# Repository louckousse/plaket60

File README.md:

# Plaket60
## Based on [Plain60 Flex Edition rev2.2](https://github.com/evyd13/plain60-flex-edition)

### Modification from Plain60 Flex Edition rev2.2

- Removing the speaker
- Removing the usb port
- Removing the flex cut
- Removing some compatibility in layout (keeping a Tsangan bottom row)

### Features
- Compatible with QMK Firmware and VIA Configurator (if you flash a VIA compatible .hex file)
- Required JST header for connection with daughterboard
- ESD protection and fuse
- No LEDs and no underglow
- Minimal layout support
- ISP header

### Supported layouts

### Bill of materials (BOM)
Amount is per PCB, multiply as needed.

| LCSC part # | Description | Value | Package  | Amount |
| ----------- | ----------- | ----- | -------- | ------:|
| C49678      | Capacitor   | 0.1uF | 0805     | 4      |
| C1779       | Capacitor   | 4.7uF | 0805     | 1      |
| C28323      | Capacitor   | 1uF   | 0805     | 1      |
| C109001     | Diode       |       | 0805     | 64     |
| C261942     | Fuse        |       | 0805     | 1      |
| C17414      | Resistor    | 10K   | 0805     | 2      |
| C212411     | Resistor    | 5.1K  | 0805     | 2      |
| C17561      | Resistor    | 22    | 0805     | 2      |
| C44854      | MCU         | 32U4  | QFP-44   | 1      |
| C7519       | ESD chip    |       | SOT23-6  | 1      |
| C341521     | Resonator   | 16MHz | SMD      | 1      |
| C92584      | Switch      |       | SMD      | 1      |
| C2845363    | JST         |       | SMD      | 1      |

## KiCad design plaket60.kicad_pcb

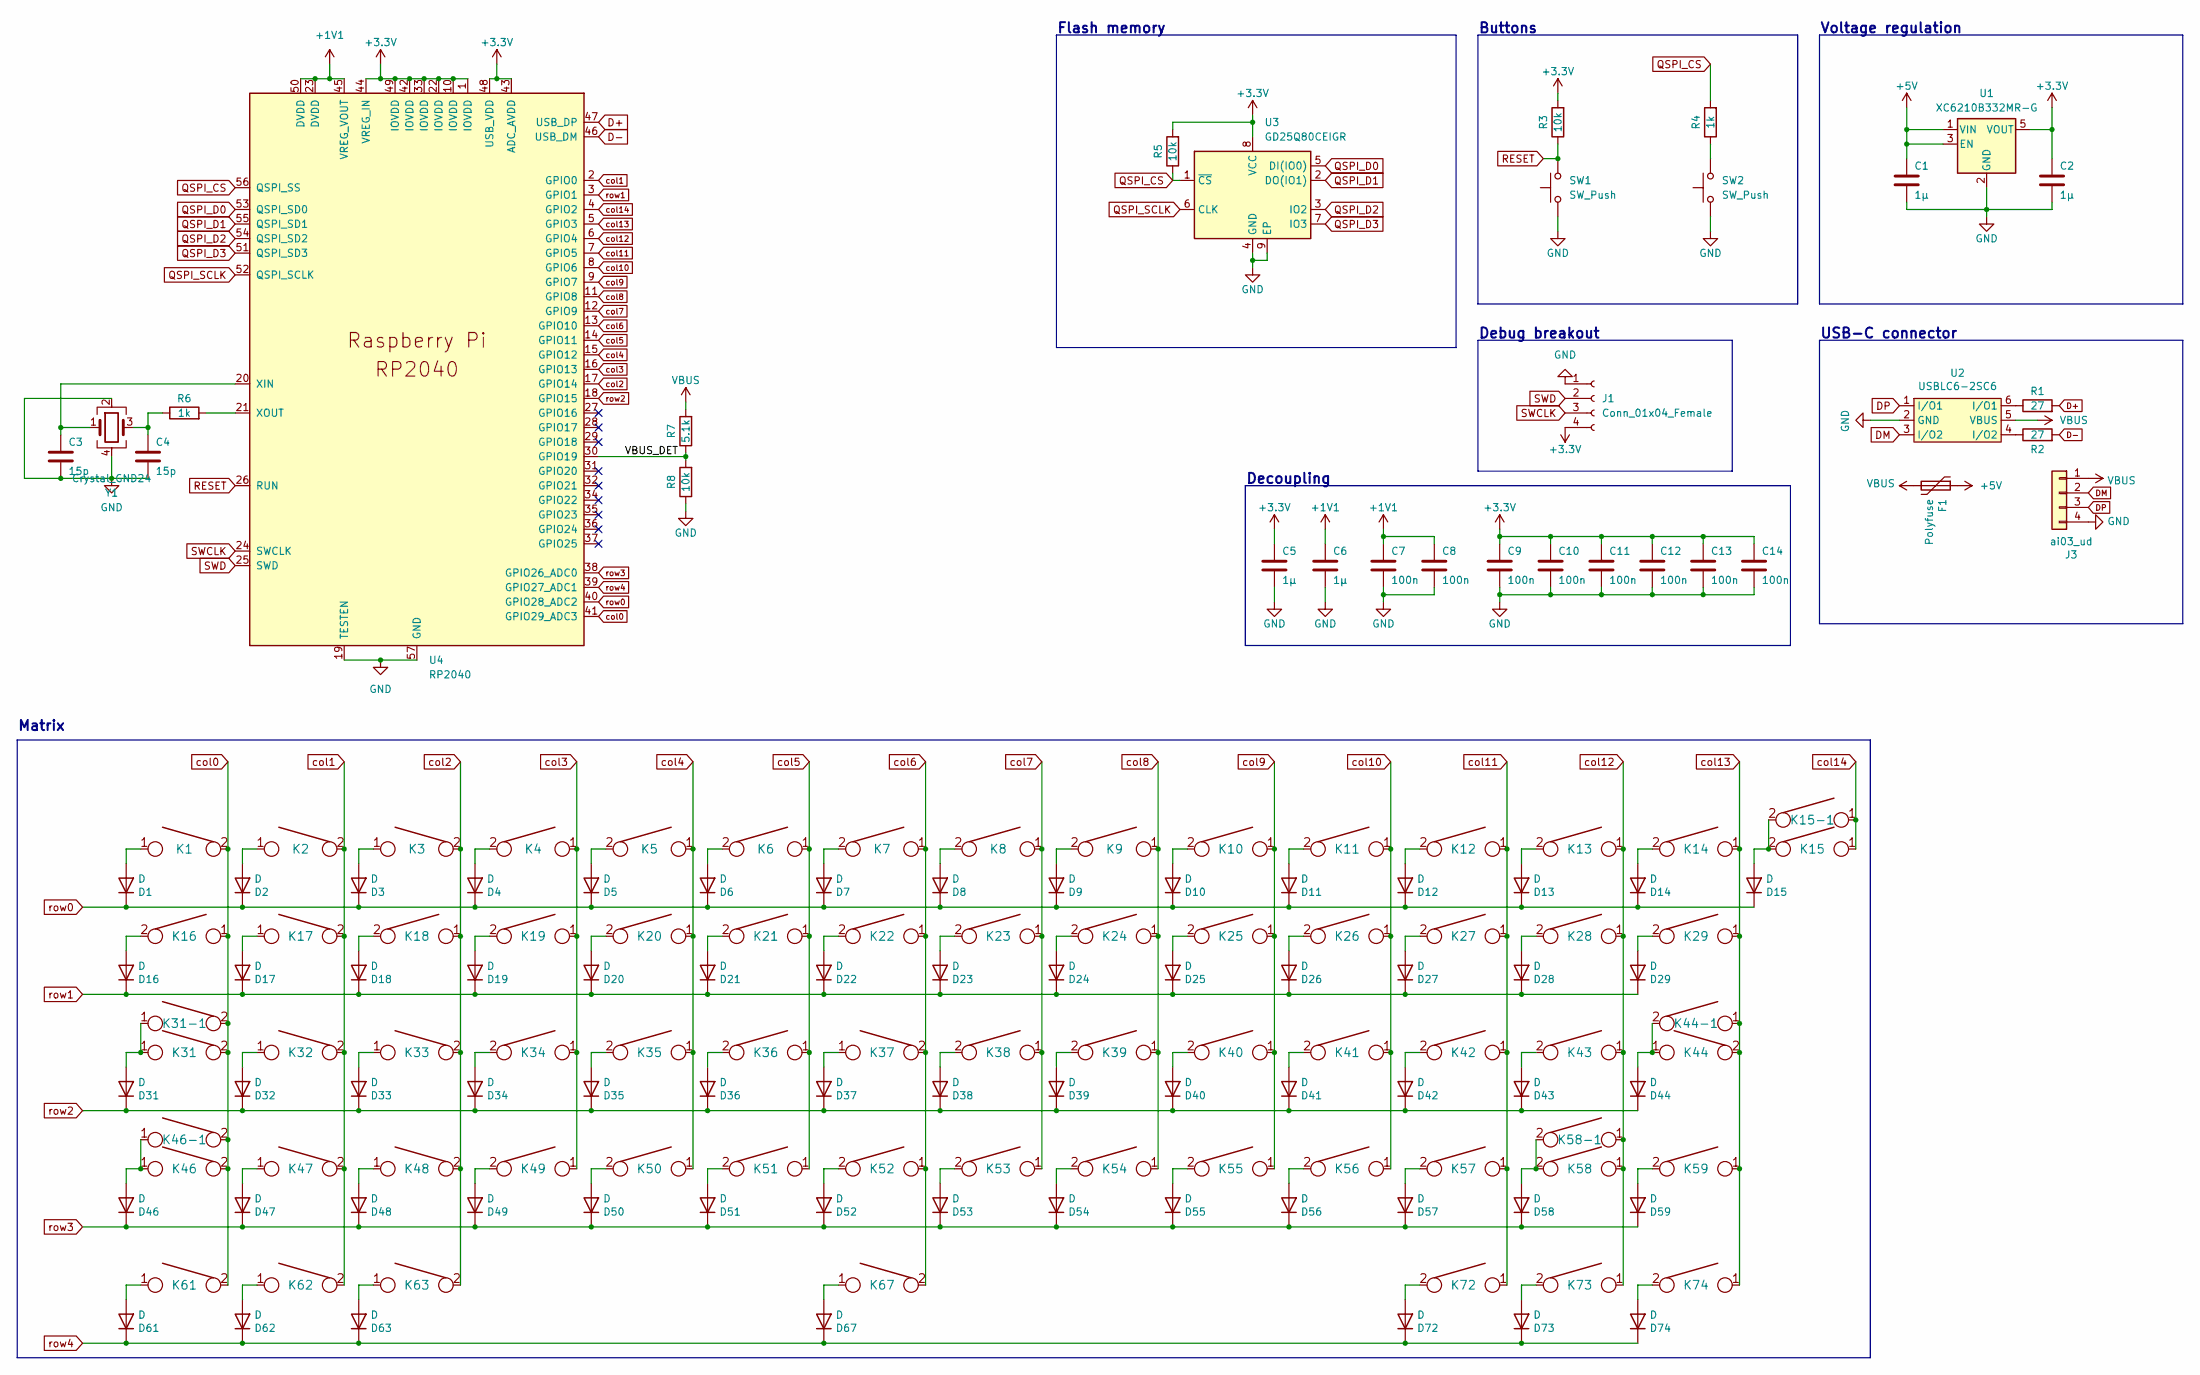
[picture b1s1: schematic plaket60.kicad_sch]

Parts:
C1, C2: 1µ; C_0402_1005Metric; LCSC C19666
C3, C4: 15p; C_0402_1005Metric; LCSC C1548
C5, C6: 1µ; C_0402_1005Metric; LCSC C52923
C7, C8, C9, C10, C11, C12, C13, C14: 100n; C_0402_1005Metric; LCSC C1525
D1, D2, D3, D4, D5, D6, D7, D8, D9, D10, D11, D12, D13, D14, D15, D16, D17, D18, D19, D20, D21, D22, D23, D24, D25, D26, D27, D28, D29, D31, D32, D33, D34, D35, D36, D37, D38, D39, D40, D41, D42, D43, D44, D46, D47, D48, D49, D50, D51, D52, D53, D54, D55, D56, D57, D58, D59, D61, D62, D63, D67, D72, D73, D74: D; D_0805
F1: Polyfuse; R_0805
J1: Conn_01x04_Female; PinHeader_1x04_P2.54mm_Vertical
J3: ai03_ud; JST_SH_SM04B-SRSS-TB_1x04-1MP_P1.00mm_Horizontal
K1, K2, K3, K4, K5, K6, K7, K8, K9, K10, K11, K12, K13, K14, K15-1, K17, K18, K19, K20, K21, K22, K23, K24, K25, K26, K27, K28, K32, K33, K34, K35, K36, K37, K38, K39, K40, K41, K42, K43, K47, K48, K49, K50, K51, K52, K53, K54, K55, K56, K57, K59, K62, K73: KEYSW; CHERRY_PLATE_100H
K15: KEYSW; CHERRY_PCB_200H
K16, K29, K61, K63, K72, K74: KEYSW; CHERRY_PLATE_150H
K31, K58-1: KEYSW; CHERRY_PLATE_175H
K31-1, K46-1: KEYSW; CHERRY_PLATE_125H
K44: KEYSW; CHERRY_PCB_225H_F
K44-1: KEYSW; CHERRY_PCB_200H_V
K46: KEYSW; CHERRY_PCB_225H
K58: KEYSW; CHERRY_PCB_275H
K67: KEYSW; CHERRY_PCB_700H_F
R1, R2: 27; R_0402_1005Metric; LCSC C25100
R3, R5, R8: 10k; R_0402_1005Metric; LCSC C25744
R4, R6: 1k; R_0402_1005Metric; LCSC C11702
R7: 5.1k; R_0402_1005Metric; LCSC C25905
SW1, SW2: SW_Push; SW_SPST_TL3342; LCSC C319433
U1: XC6210B332MR-G; SOT-23-5; LCSC C82942
U2: USBLC6-2SC6; Farnell 1295310
U3: GD25Q80CEIGR; USON-8-1EP_3x2mm_P0.5mm_EP0.25x1.65mm; LCSC C395484
U4: RP2040; RP2040-QFN-56
Y1: Crystal_GND24; Crystal_SMD_3225-4Pin_3.2x2.5mm

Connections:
+1V1: C6.1, C7.1, C8.1, U4.23 (DVDD), U4.45 (VREG_VOUT), U4.50 (DVDD)
+3V3: C2.1, C5.1, C9.1, C10.1, C11.1, C12.1, C13.1, C14.1, J1.4, R3.2, R5.2, U1.5 (VOUT), U3.8 (VCC), U4.1 (IOVDD), U4.10 (IOVDD), U4.22 (IOVDD), U4.33 (IOVDD), U4.42 (IOVDD), U4.43 (ADC_AVDD), U4.44 (VREG_IN), U4.48 (USB_VDD), U4.49 (IOVDD)
+5V: C1.1, F1.1, U1.1 (VIN), U1.3 (EN)
/VBUS_DET: R7.1, R8.2, U4.30 (GPIO19)
D+: R1.2, U4.47 (USB_DP)
D-: R2.2, U4.46 (USB_DM)
DM: J3.2, U2.3 (I/O2)
DP: J3.3, U2.1 (I/O1)
GND: C1.2, C2.2, C3.2, C4.2, C5.2, C6.2, C7.2, C8.2, C9.2, C10.2, C11.2, C12.2, C13.2, C14.2, J1.1, J3.4, R8.1, SW1.1, SW2.1, U1.2 (GND), U2.2 (GND), U3.4 (GND), U3.9 (EP), U4.19 (TESTEN), U4.57 (GND), Y1.2, Y1.4
unnamed: C3.1, U4.20 (XIN), Y1.1
unnamed: C4.1, R6.1, Y1.3
unnamed: D1.2 (A), K1.1
unnamed: D2.2 (A), K2.1
unnamed: D3.2 (A), K3.1
unnamed: D4.2 (A), K4.2
unnamed: D5.2 (A), K5.2
unnamed: D6.2 (A), K6.2
unnamed: D7.2 (A), K7.2
unnamed: D8.2 (A), K8.2
unnamed: D9.2 (A), K9.2
unnamed: D10.2 (A), K10.2
unnamed: D11.2 (A), K11.2
unnamed: D12.2 (A), K12.2
unnamed: D13.2 (A), K13.2
unnamed: D14.2 (A), K14.2
unnamed: D15.2 (A), K15.2, K15-1.2
unnamed: D16.2 (A), K16.2
unnamed: D17.2 (A), K17.1
unnamed: D18.2 (A), K18.2
unnamed: D19.2 (A), K19.2
unnamed: D20.2 (A), K20.2
unnamed: D21.2 (A), K21.2
unnamed: D22.2 (A), K22.2
unnamed: D23.2 (A), K23.2
unnamed: D24.2 (A), K24.2
unnamed: D25.2 (A), K25.2
unnamed: D26.2 (A), K26.2
unnamed: D27.2 (A), K27.2
unnamed: D28.2 (A), K28.2
unnamed: D29.2 (A), K29.2
unnamed: D31.2 (A), K31.1, K31-1.1
unnamed: D32.2 (A), K32.1
unnamed: D33.2 (A), K33.1
unnamed: D34.2 (A), K34.2
unnamed: D35.2 (A), K35.2
unnamed: D36.2 (A), K36.2
unnamed: D37.2 (A), K37.1
unnamed: D38.2 (A), K38.2
unnamed: D39.2 (A), K39.2
unnamed: D40.2 (A), K40.2
unnamed: D41.2 (A), K41.2
unnamed: D42.2 (A), K42.2
unnamed: D43.2 (A), K43.2
unnamed: D44.2 (A), K44.1, K44-1.2
unnamed: D46.2 (A), K46.1, K46-1.1
unnamed: D47.2 (A), K47.1
unnamed: D48.2 (A), K48.1
unnamed: D49.2 (A), K49.2
unnamed: D50.2 (A), K50.2
unnamed: D51.2 (A), K51.2
unnamed: D52.2 (A), K52.2
unnamed: D53.2 (A), K53.2
unnamed: D54.2 (A), K54.2
unnamed: D55.2 (A), K55.2
unnamed: D56.2 (A), K56.2
unnamed: D57.2 (A), K57.2
unnamed: D58.2 (A), K58.2, K58-1.2
unnamed: D59.2 (A), K59.2
unnamed: D61.2 (A), K61.1
unnamed: D62.2 (A), K62.1
unnamed: D63.2 (A), K63.1
unnamed: D67.2 (A), K67.1
unnamed: D72.2 (A), K72.2
unnamed: D73.2 (A), K73.2
unnamed: D74.2 (A), K74.2
unnamed: R1.1, U2.6 (I/O1)
unnamed: R2.1, U2.4 (I/O2)
unnamed: R4.1, SW2.2
unnamed: R6.2, U4.21 (XOUT)
QSPI_CS: R4.2, R5.1, U3.1 (~CS), U4.56 (QSPI_SS)
QSPI_D0: U3.5 (DI(IO0)), U4.53 (QSPI_SD0)
QSPI_D1: U3.2 (DO(IO1)), U4.55 (QSPI_SD1)
QSPI_D2: U3.3 (IO2), U4.54 (QSPI_SD2)
QSPI_D3: U3.7 (IO3), U4.51 (QSPI_SD3)
QSPI_SCLK: U3.6 (CLK), U4.52 (QSPI_SCLK)
RESET: R3.1, SW1.2, U4.26 (RUN)
SWCLK: J1.3, U4.24 (SWCLK)
SWD: J1.2, U4.25 (SWD)
VBUS: F1.2, J3.1, R7.2, U2.5 (VBUS)
col0: K1.2, K16.1, K31.2, K31-1.2, K46.2, K46-1.2, K61.2, U4.41 (GPIO29_ADC3)
col1: K2.2, K17.2, K32.2, K47.2, K62.2, U4.2 (GPIO0)
col2: K3.2, K18.1, K33.2, K48.2, K63.2, U4.17 (GPIO14)
col3: K4.1, K19.1, K34.1, K49.1, U4.16 (GPIO13)
col4: K5.1, K20.1, K35.1, K50.1, U4.15 (GPIO12)
col5: K6.1, K21.1, K36.1, K51.1, U4.14 (GPIO11)
col6: K7.1, K22.1, K37.2, K52.1, K67.2, U4.13 (GPIO10)
col7: K8.1, K23.1, K38.1, K53.1, U4.12 (GPIO9)
col8: K9.1, K24.1, K39.1, K54.1, U4.11 (GPIO8)
col9: K10.1, K25.1, K40.1, K55.1, U4.9 (GPIO7)
col10: K11.1, K26.1, K41.1, K56.1, U4.8 (GPIO6)
col11: K12.1, K27.1, K42.1, K57.1, K72.1, U4.7 (GPIO5)
col12: K13.1, K28.1, K43.1, K58.1, K58-1.1, K73.1, U4.6 (GPIO4)
col13: K14.1, K29.1, K44.2, K44-1.1, K59.1, K74.1, U4.5 (GPIO3)
col14: K15.1, K15-1.1, U4.4 (GPIO2)
row0: D1.1 (K), D2.1 (K), D3.1 (K), D4.1 (K), D5.1 (K), D6.1 (K), D7.1 (K), D8.1 (K), D9.1 (K), D10.1 (K), D11.1 (K), D12.1 (K), D13.1 (K), D14.1 (K), D15.1 (K), U4.40 (GPIO28_ADC2)
row1: D16.1 (K), D17.1 (K), D18.1 (K), D19.1 (K), D20.1 (K), D21.1 (K), D22.1 (K), D23.1 (K), D24.1 (K), D25.1 (K), D26.1 (K), D27.1 (K), D28.1 (K), D29.1 (K), U4.3 (GPIO1)
row2: D31.1 (K), D32.1 (K), D33.1 (K), D34.1 (K), D35.1 (K), D36.1 (K), D37.1 (K), D38.1 (K), D39.1 (K), D40.1 (K), D41.1 (K), D42.1 (K), D43.1 (K), D44.1 (K), U4.18 (GPIO15)
row3: D46.1 (K), D47.1 (K), D48.1 (K), D49.1 (K), D50.1 (K), D51.1 (K), D52.1 (K), D53.1 (K), D54.1 (K), D55.1 (K), D56.1 (K), D57.1 (K), D58.1 (K), D59.1 (K), U4.38 (GPIO26_ADC0)
row4: D61.1 (K), D62.1 (K), D63.1 (K), D67.1 (K), D72.1 (K), D73.1 (K), D74.1 (K), U4.39 (GPIO27_ADC1)

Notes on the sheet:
Buttons
Voltage regulation
Flash memory
Decoupling
USB-C connector
Matrix
Debug breakout

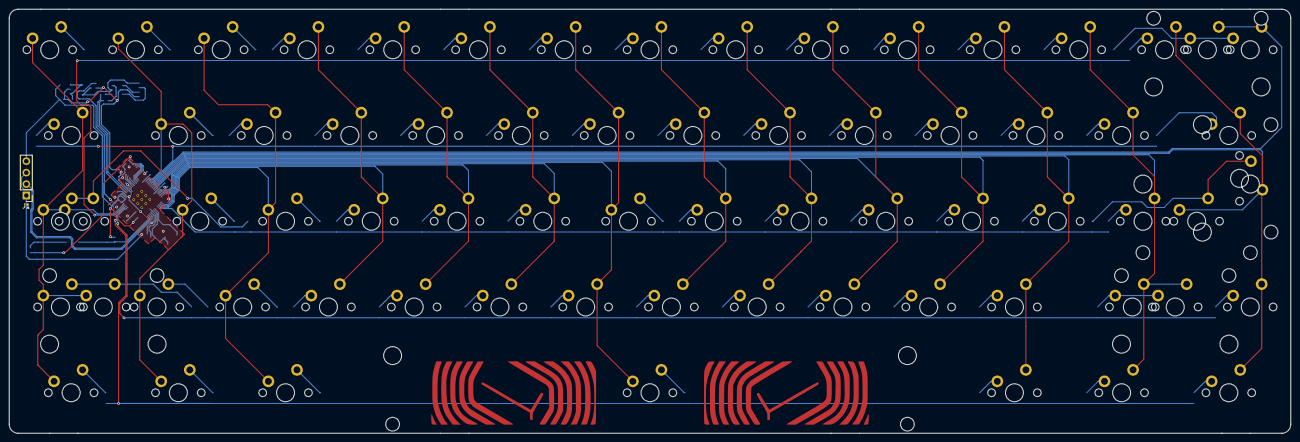
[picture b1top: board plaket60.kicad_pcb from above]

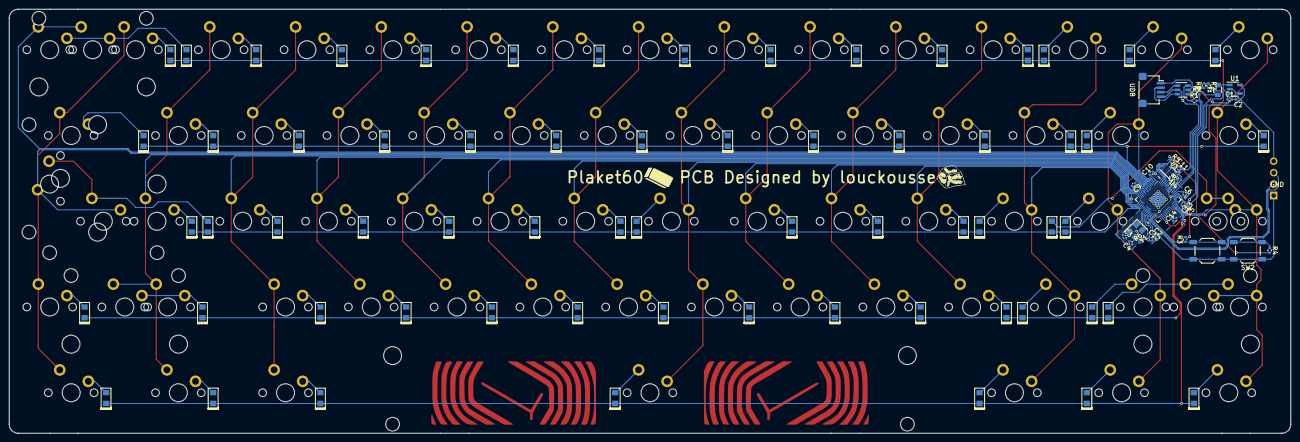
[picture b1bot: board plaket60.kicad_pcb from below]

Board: 2 copper layers, 284.7 x 94.2 mm, 165 parts (95 on the bottom side), 109 nets.

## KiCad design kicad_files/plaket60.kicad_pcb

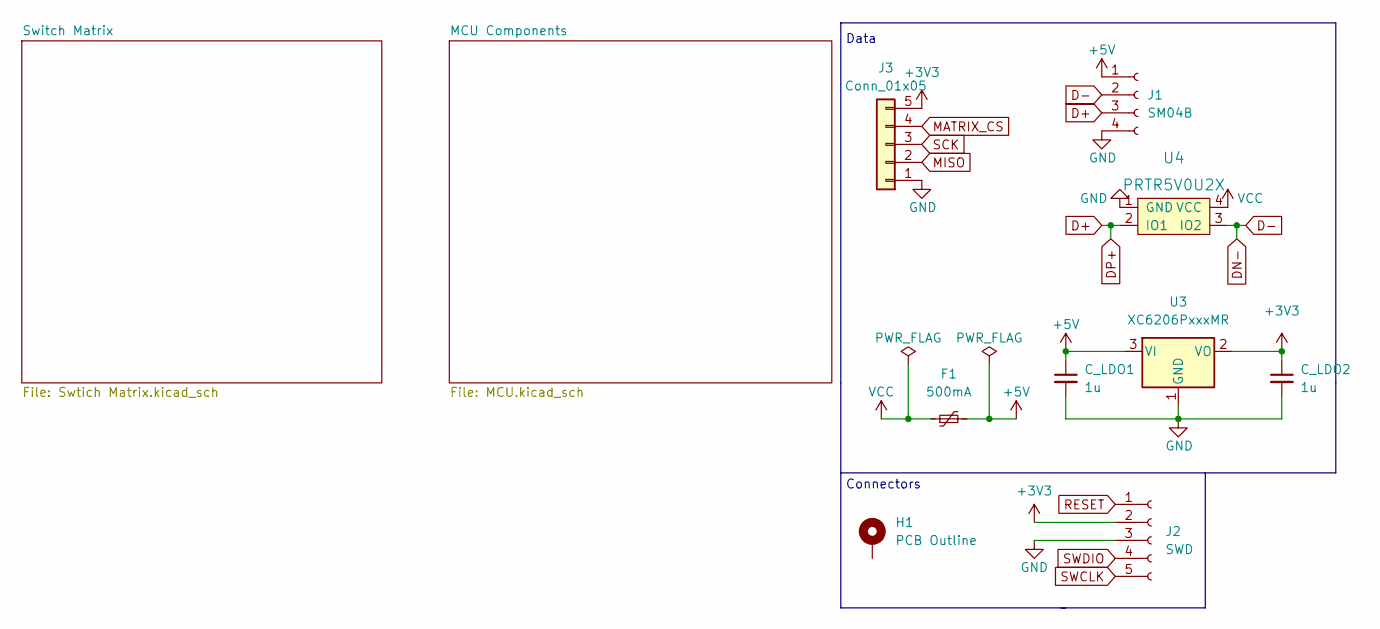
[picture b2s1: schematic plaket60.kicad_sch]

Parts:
C_LDO1, C_LDO2: 1u; C_0402_1005Metric
F1: 500mA; Fuse_0805_2012Metric
H1: PCB Outline; L60 Outline
J1: SM04B; JST_SH_SM04B-SRSS-TB_1x04-1MP_P1.00mm_Horizontal
J2: SWD; PinHeader_1x05_P2.54mm_Vertical
J3: Conn_01x05; JST_SH_SM05B-SRSS-TB_1x05-1MP_P1.00mm_Horizontal
U3: XC6206PxxxMR; SOT-23
U4: PRTR5V0U2X; SOT143B

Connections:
+3V3: C_LDO2.1, J2.2, J3.5, U3.2 (VO); also elsewhere on the board
+5V: C_LDO1.1, F1.2, J1.1, U3.3 (VI)
D+: J1.3, U4.2 (IO1); also elsewhere on the board
D-: J1.2, U4.3 (IO2); also elsewhere on the board
GND: C_LDO1.2, C_LDO2.2, J1.4, J2.3, J3.1, U3.1 (GND), U4.1 (GND); also elsewhere on the board
MATRIX_CS: J3.4; also elsewhere on the board
MISO: J3.2; also elsewhere on the board
RESET: J2.1; also elsewhere on the board
SCK: J3.3; also elsewhere on the board
SWCLK: J2.5; also elsewhere on the board
SWDIO: J2.4; also elsewhere on the board
VCC: F1.1, U4.4 (VCC)

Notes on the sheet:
Connectors
Data

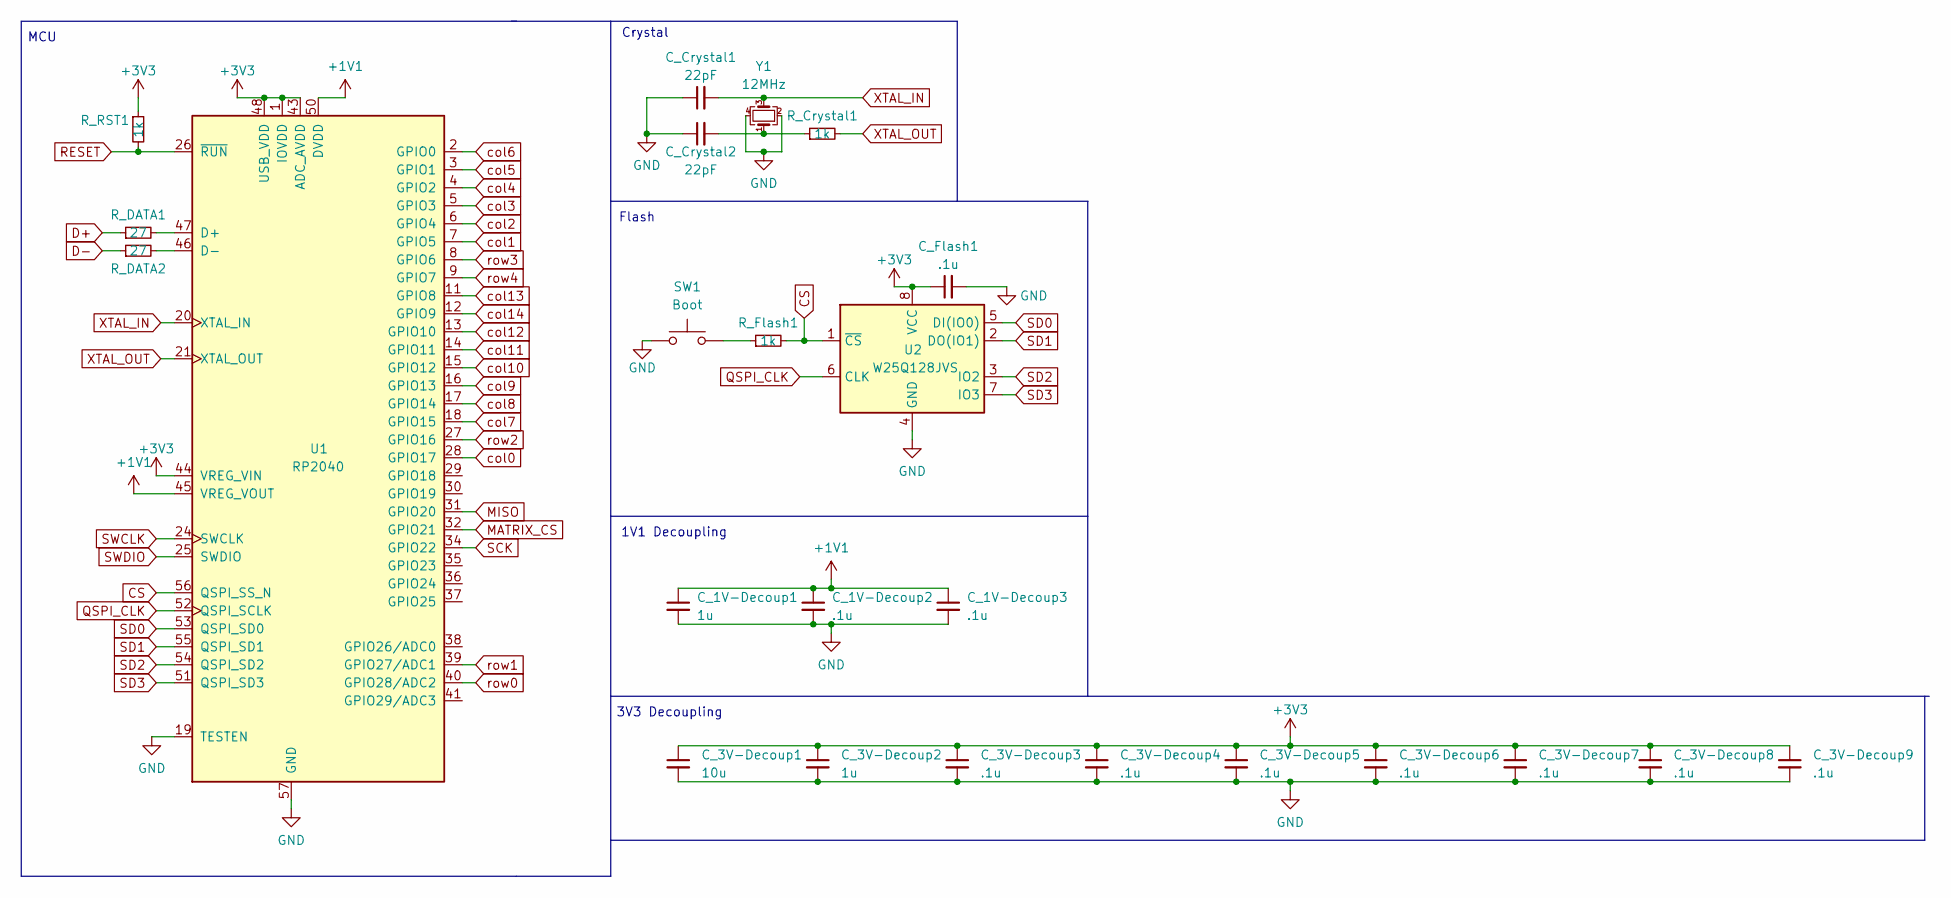
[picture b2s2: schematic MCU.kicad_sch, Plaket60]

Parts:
C_1V-Decoup1, C_3V-Decoup2: 1u; C_0402_1005Metric
C_1V-Decoup2, C_1V-Decoup3, C_3V-Decoup3, C_3V-Decoup4, C_3V-Decoup5, C_3V-Decoup6, C_3V-Decoup7, C_3V-Decoup8, C_3V-Decoup9: .1u; C_0402_1005Metric
C_3V-Decoup1: 10u; C_0402_1005Metric
C_Crystal1, C_Crystal2: 22pF; C_0402_1005Metric
C_Flash1: .1u; C_0402_1005Metric
R_Crystal1: 1k; R_0402_1005Metric
R_DATA1, R_DATA2: 27; R_0402_1005Metric
R_Flash1: 1k; R_0402_1005Metric
R_RST1: 1k; R_0402_1005Metric
SW1: Boot; PinHeader_1x02_P2.54mm_Vertical
U1: RP2040; RP2040-QFN-56
U2: W25Q128JVS; SOIC-8_5.23x5.23mm_P1.27mm
Y1: 12MHz; Crystal_SMD_3225-4Pin_3.2x2.5mm

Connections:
+1V1: C_1V-Decoup1.1, C_1V-Decoup2.1, C_1V-Decoup3.1, U1.23 (DVDD), U1.45 (VREG_VOUT), U1.50 (DVDD)
+3V3: C_3V-Decoup1.1, C_3V-Decoup2.1, C_3V-Decoup3.1, C_3V-Decoup4.1, C_3V-Decoup5.1, C_3V-Decoup6.1, C_3V-Decoup7.1, C_3V-Decoup8.1, C_3V-Decoup9.1, C_Flash1.1, R_RST1.1, U1.1 (IOVDD), U1.10 (IOVDD), U1.22 (IOVDD), U1.33 (IOVDD), U1.42 (IOVDD), U1.43 (ADC_AVDD), U1.44 (VREG_VIN), U1.48 (USB_VDD), U1.49 (IOVDD), U2.8 (VCC); also elsewhere on the board
CS: R_Flash1.2, U1.56 (QSPI_SS_N), U2.1 (~CS)
D+: R_DATA1.1; also elsewhere on the board
D-: R_DATA2.1; also elsewhere on the board
GND: C_1V-Decoup1.2, C_1V-Decoup2.2, C_1V-Decoup3.2, C_3V-Decoup1.2, C_3V-Decoup2.2, C_3V-Decoup3.2, C_3V-Decoup4.2, C_3V-Decoup5.2, C_3V-Decoup6.2, C_3V-Decoup7.2, C_3V-Decoup8.2, C_3V-Decoup9.2, C_Crystal1.1, C_Crystal2.1, C_Flash1.2, SW1.1, U1.19 (TESTEN), U1.57 (GND), U2.4 (GND), Y1.2, Y1.4; also elsewhere on the board
MATRIX_CS: U1.32 (GPIO21); also elsewhere on the board
MISO: U1.31 (GPIO20); also elsewhere on the board
unnamed: C_Crystal2.2, R_Crystal1.1, Y1.1
unnamed: R_Flash1.1, SW1.2
unnamed: R_DATA1.2, U1.47 (D+)
unnamed: R_DATA2.2, U1.46 (D-)
QSPI_CLK: U1.52 (QSPI_SCLK), U2.6 (CLK)
RESET: R_RST1.2, U1.26 (~RUN); also elsewhere on the board
SCK: U1.34 (GPIO22); also elsewhere on the board
SD0: U1.53 (QSPI_SD0), U2.5 (DI(IO0))
SD1: U1.55 (QSPI_SD1), U2.2 (DO(IO1))
SD2: U1.54 (QSPI_SD2), U2.3 (IO2)
SD3: U1.51 (QSPI_SD3), U2.7 (IO3)
SWCLK: U1.24 (SWCLK); also elsewhere on the board
SWDIO: U1.25 (SWDIO); also elsewhere on the board
XTAL_IN: C_Crystal1.2, U1.20 (XTAL_IN), Y1.3
XTAL_OUT: R_Crystal1.2, U1.21 (XTAL_OUT)
col0: U1.28 (GPIO17); also elsewhere on the board
col1: U1.7 (GPIO5); also elsewhere on the board
col2: U1.6 (GPIO4); also elsewhere on the board
col3: U1.5 (GPIO3); also elsewhere on the board
col4: U1.4 (GPIO2); also elsewhere on the board
col5: U1.3 (GPIO1); also elsewhere on the board
col6: U1.2 (GPIO0); also elsewhere on the board
col7: U1.18 (GPIO15); also elsewhere on the board
col8: U1.17 (GPIO14); also elsewhere on the board
col9: U1.16 (GPIO13); also elsewhere on the board
col10: U1.15 (GPIO12); also elsewhere on the board
col11: U1.14 (GPIO11); also elsewhere on the board
col12: U1.13 (GPIO10); also elsewhere on the board
col13: U1.11 (GPIO8); also elsewhere on the board
col14: U1.12 (GPIO9); also elsewhere on the board
row0: U1.40 (GPIO28/ADC2); also elsewhere on the board
row1: U1.39 (GPIO27/ADC1); also elsewhere on the board
row2: U1.27 (GPIO16); also elsewhere on the board
row3: U1.8 (GPIO6); also elsewhere on the board
row4: U1.9 (GPIO7); also elsewhere on the board

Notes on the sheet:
Flash
MCU
Crystal
3V3 Decoupling
1V1 Decoupling

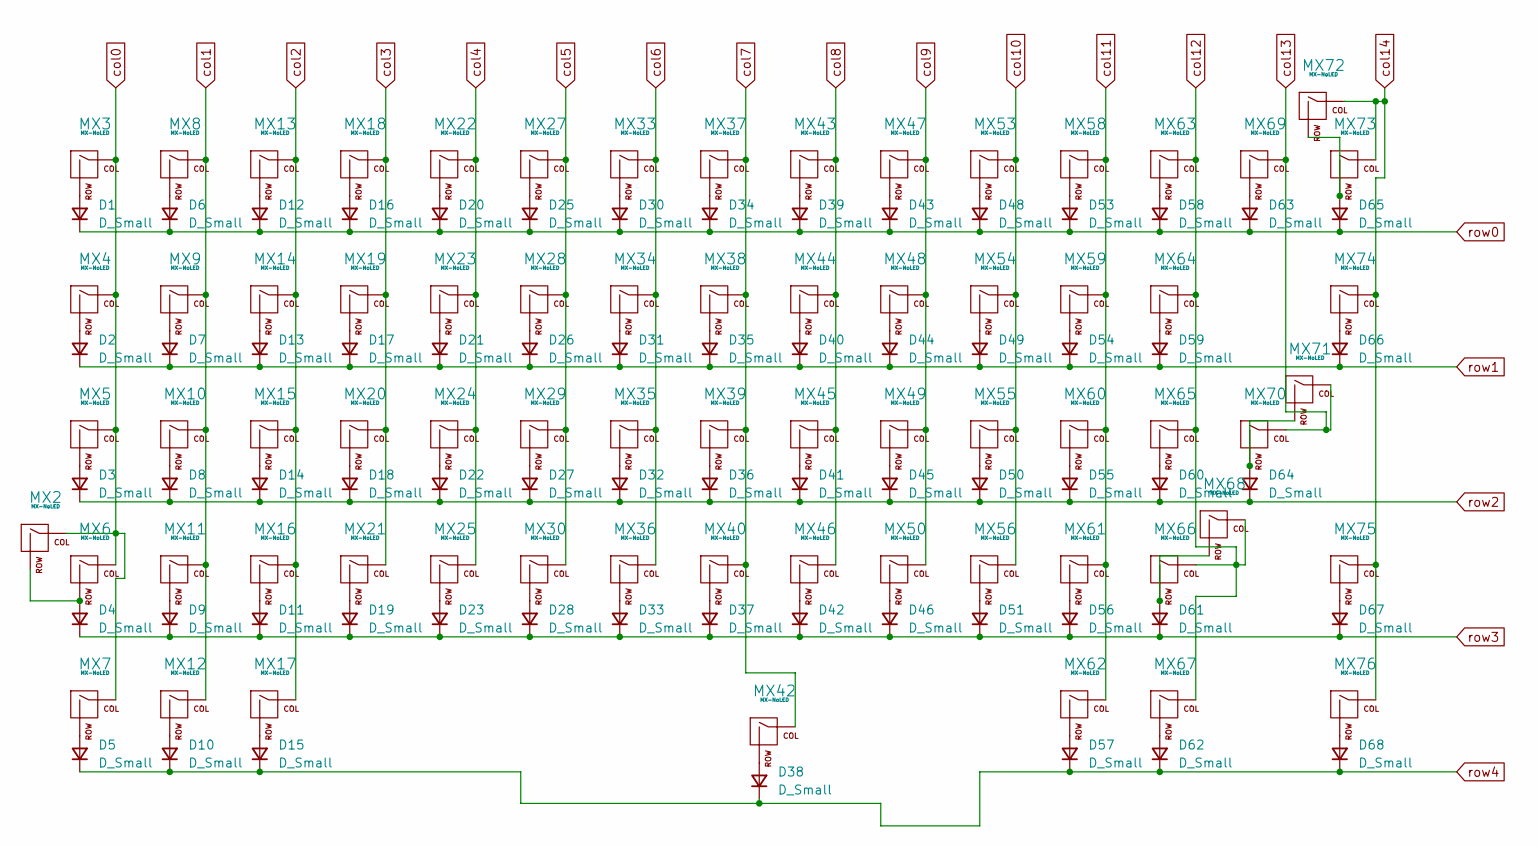
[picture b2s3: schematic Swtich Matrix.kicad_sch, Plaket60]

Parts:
D1, D2, D3, D4, D5, D6, D7, D8, D9, D10, D11, D12, D13, D14, D15, D16, D17, D18, D19, D20, D21, D22, D23, D25, D26, D27, D28, D30, D31, D32, D33, D34, D35, D36, D37, D38, D39, D40, D41, D42, D43, D44, D45, D46, D48, D49, D50, D51, D53, D54, D55, D56, D57, D58, D59, D60, D61, D62, D63, D64, D65, D66, D67, D68: D_Small; D_SOD-123
MX2: MX-NoLED; mx_125u
MX3, MX8, MX9, MX10, MX11, MX12, MX13, MX14, MX15, MX16, MX18, MX19, MX20, MX21, MX22, MX23, MX24, MX25, MX27, MX28, MX29, MX30, MX33, MX34, MX35, MX36, MX37, MX38, MX39, MX40, MX43, MX44, MX45, MX46, MX47, MX48, MX49, MX50, MX53, MX54, MX55, MX56, MX58, MX59, MX60, MX61, MX63, MX64, MX65, MX67, MX69, MX73, MX75: MX-NoLED; mx_1u
MX4, MX7, MX17, MX62, MX74, MX76: MX-NoLED; mx_15u
MX5: MX-NoLED; mx_stepped_caps
MX6, MX70: MX-NoLED; mx_225u
MX42: MX-NoLED; mx_7u
MX66: MX-NoLED; mx_175u
MX68: MX-NoLED; mx_275u
MX71: MX-NoLED; mx_iso
MX72: MX-NoLED; mx_2u

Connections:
unnamed: D1.2 (A), MX3.2 (ROW)
unnamed: D2.2 (A), MX4.2 (ROW)
unnamed: D3.2 (A), MX5.2 (ROW)
unnamed: D4.2 (A), MX2.2 (ROW), MX6.2 (ROW)
unnamed: D5.2 (A), MX7.2 (ROW)
unnamed: D6.2 (A), MX8.2 (ROW)
unnamed: D7.2 (A), MX9.2 (ROW)
unnamed: D8.2 (A), MX10.2 (ROW)
unnamed: D9.2 (A), MX11.2 (ROW)
unnamed: D10.2 (A), MX12.2 (ROW)
unnamed: D11.2 (A), MX16.2 (ROW)
unnamed: D12.2 (A), MX13.2 (ROW)
unnamed: D13.2 (A), MX14.2 (ROW)
unnamed: D14.2 (A), MX15.2 (ROW)
unnamed: D15.2 (A), MX17.2 (ROW)
unnamed: D16.2 (A), MX18.2 (ROW)
unnamed: D17.2 (A), MX19.2 (ROW)
unnamed: D18.2 (A), MX20.2 (ROW)
unnamed: D19.2 (A), MX21.2 (ROW)
unnamed: D20.2 (A), MX22.2 (ROW)
unnamed: D21.2 (A), MX23.2 (ROW)
unnamed: D22.2 (A), MX24.2 (ROW)
unnamed: D23.2 (A), MX25.2 (ROW)
unnamed: D25.2 (A), MX27.2 (ROW)
unnamed: D26.2 (A), MX28.2 (ROW)
unnamed: D27.2 (A), MX29.2 (ROW)
unnamed: D28.2 (A), MX30.2 (ROW)
unnamed: D30.2 (A), MX33.2 (ROW)
unnamed: D31.2 (A), MX34.2 (ROW)
unnamed: D32.2 (A), MX35.2 (ROW)
unnamed: D33.2 (A), MX36.2 (ROW)
unnamed: D34.2 (A), MX37.2 (ROW)
unnamed: D35.2 (A), MX38.2 (ROW)
unnamed: D36.2 (A), MX39.2 (ROW)
unnamed: D37.2 (A), MX40.2 (ROW)
unnamed: D38.2 (A), MX42.2 (ROW)
unnamed: D39.2 (A), MX43.2 (ROW)
unnamed: D40.2 (A), MX44.2 (ROW)
unnamed: D41.2 (A), MX45.2 (ROW)
unnamed: D42.2 (A), MX46.2 (ROW)
unnamed: D43.2 (A), MX47.2 (ROW)
unnamed: D44.2 (A), MX48.2 (ROW)
unnamed: D45.2 (A), MX49.2 (ROW)
unnamed: D46.2 (A), MX50.2 (ROW)
unnamed: D48.2 (A), MX53.2 (ROW)
unnamed: D49.2 (A), MX54.2 (ROW)
unnamed: D50.2 (A), MX55.2 (ROW)
unnamed: D51.2 (A), MX56.2 (ROW)
unnamed: D53.2 (A), MX58.2 (ROW)
unnamed: D54.2 (A), MX59.2 (ROW)
unnamed: D55.2 (A), MX60.2 (ROW)
unnamed: D56.2 (A), MX61.2 (ROW)
unnamed: D57.2 (A), MX62.2 (ROW)
unnamed: D58.2 (A), MX63.2 (ROW)
unnamed: D59.2 (A), MX64.2 (ROW)
unnamed: D60.2 (A), MX65.2 (ROW)
unnamed: D61.2 (A), MX66.2 (ROW), MX68.2 (ROW)
unnamed: D62.2 (A), MX67.2 (ROW)
unnamed: D63.2 (A), MX69.2 (ROW)
unnamed: D64.2 (A), MX70.2 (ROW), MX71.2 (ROW)
unnamed: D65.2 (A), MX72.2 (ROW), MX73.2 (ROW)
unnamed: D66.2 (A), MX74.2 (ROW)
unnamed: D67.2 (A), MX75.2 (ROW)
unnamed: D68.2 (A), MX76.2 (ROW)
col0: MX2.1 (COL), MX3.1 (COL), MX4.1 (COL), MX5.1 (COL), MX6.1 (COL), MX7.1 (COL); also elsewhere on the board
col1: MX8.1 (COL), MX9.1 (COL), MX10.1 (COL), MX11.1 (COL), MX12.1 (COL); also elsewhere on the board
col2: MX13.1 (COL), MX14.1 (COL), MX15.1 (COL), MX16.1 (COL), MX17.1 (COL); also elsewhere on the board
col3: MX18.1 (COL), MX19.1 (COL), MX20.1 (COL), MX21.1 (COL); also elsewhere on the board
col4: MX22.1 (COL), MX23.1 (COL), MX24.1 (COL), MX25.1 (COL); also elsewhere on the board
col5: MX27.1 (COL), MX28.1 (COL), MX29.1 (COL), MX30.1 (COL); also elsewhere on the board
col6: MX33.1 (COL), MX34.1 (COL), MX35.1 (COL), MX36.1 (COL); also elsewhere on the board
col7: MX37.1 (COL), MX38.1 (COL), MX39.1 (COL), MX40.1 (COL), MX42.1 (COL); also elsewhere on the board
col8: MX43.1 (COL), MX44.1 (COL), MX45.1 (COL), MX46.1 (COL); also elsewhere on the board
col9: MX47.1 (COL), MX48.1 (COL), MX49.1 (COL), MX50.1 (COL); also elsewhere on the board
col10: MX53.1 (COL), MX54.1 (COL), MX55.1 (COL), MX56.1 (COL); also elsewhere on the board
col11: MX58.1 (COL), MX59.1 (COL), MX60.1 (COL), MX61.1 (COL), MX62.1 (COL); also elsewhere on the board
col12: MX63.1 (COL), MX64.1 (COL), MX65.1 (COL), MX66.1 (COL), MX67.1 (COL), MX68.1 (COL); also elsewhere on the board
col13: MX69.1 (COL), MX70.1 (COL), MX71.1 (COL); also elsewhere on the board
col14: MX72.1 (COL), MX73.1 (COL), MX74.1 (COL), MX75.1 (COL), MX76.1 (COL); also elsewhere on the board
row0: D1.1 (K), D6.1 (K), D12.1 (K), D16.1 (K), D20.1 (K), D25.1 (K), D30.1 (K), D34.1 (K), D39.1 (K), D43.1 (K), D48.1 (K), D53.1 (K), D58.1 (K), D63.1 (K), D65.1 (K); also elsewhere on the board
row1: D2.1 (K), D7.1 (K), D13.1 (K), D17.1 (K), D21.1 (K), D26.1 (K), D31.1 (K), D35.1 (K), D40.1 (K), D44.1 (K), D49.1 (K), D54.1 (K), D59.1 (K), D66.1 (K); also elsewhere on the board
row2: D3.1 (K), D8.1 (K), D14.1 (K), D18.1 (K), D22.1 (K), D27.1 (K), D32.1 (K), D36.1 (K), D41.1 (K), D45.1 (K), D50.1 (K), D55.1 (K), D60.1 (K), D64.1 (K); also elsewhere on the board
row3: D4.1 (K), D9.1 (K), D11.1 (K), D19.1 (K), D23.1 (K), D28.1 (K), D33.1 (K), D37.1 (K), D42.1 (K), D46.1 (K), D51.1 (K), D56.1 (K), D61.1 (K), D67.1 (K); also elsewhere on the board
row4: D5.1 (K), D10.1 (K), D15.1 (K), D38.1 (K), D57.1 (K), D62.1 (K), D68.1 (K); also elsewhere on the board

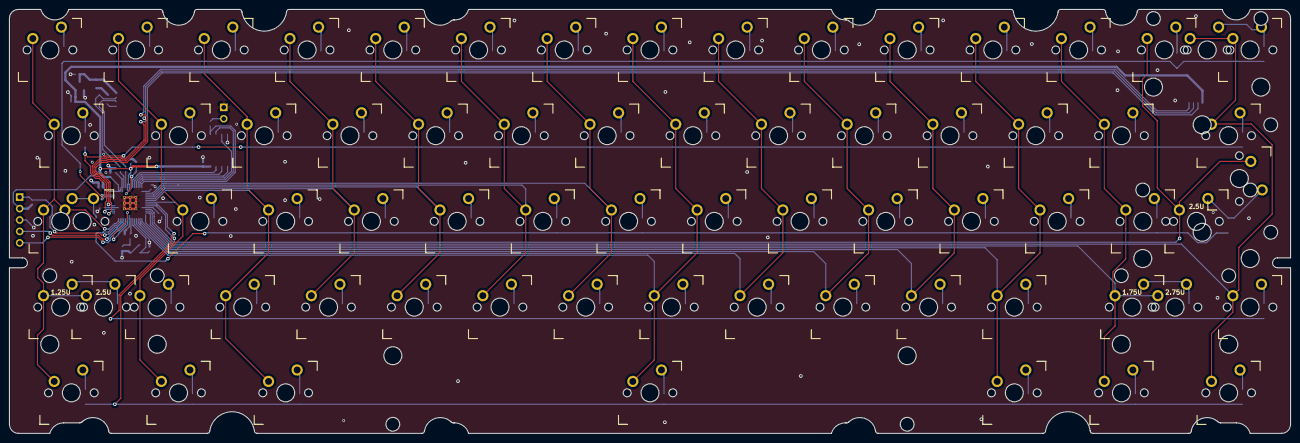
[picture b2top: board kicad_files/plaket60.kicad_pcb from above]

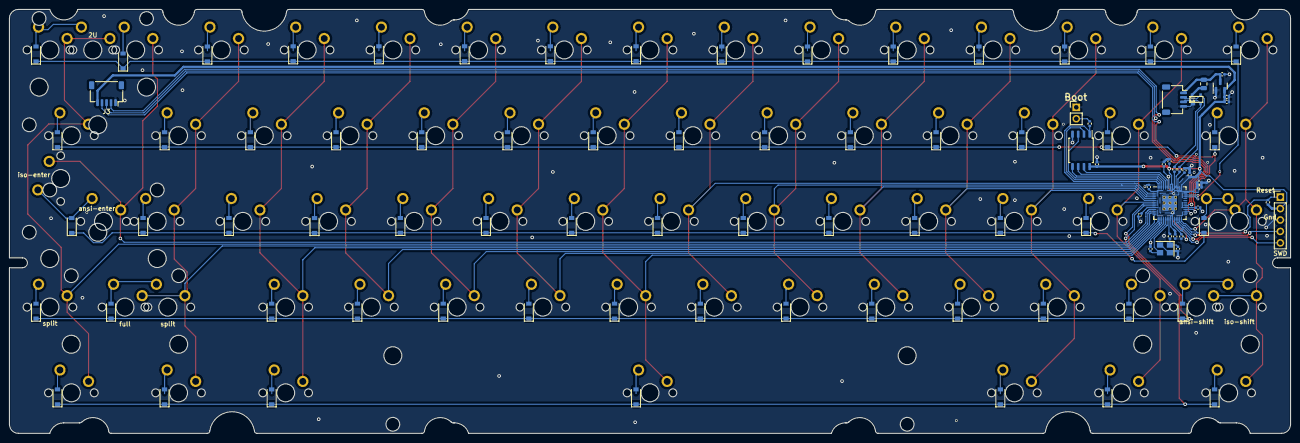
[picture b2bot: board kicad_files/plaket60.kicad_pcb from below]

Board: 2 copper layers, 284.7 x 94.2 mm, 165 parts (96 on the bottom side), 109 nets.

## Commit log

2022-08-08 over
2022-12-06 last commit on atmega32u4
2023-01-19 :shower:
2023-01-22 2U stabs position
2023-01-25 go to jlcpcb
2023-01-28 good base
2023-01-30 j'sais pas
2023-02-10 ready for GB
2023-03-19 update lib
2023-04-08 double jst
2023-06-26 /shrug
